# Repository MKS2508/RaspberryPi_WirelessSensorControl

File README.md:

# RaspberryPi_WirelessSensorControl

**Apache server running on a _raspberry pi_ displaying data received by sensors(arduino) over zigbee protocol**

*Sensor 1: Battery powered wireless temperature & humidity sensor board: DHT11 + Arduino pro mini + Xbee*

          Front side:

          Back side:

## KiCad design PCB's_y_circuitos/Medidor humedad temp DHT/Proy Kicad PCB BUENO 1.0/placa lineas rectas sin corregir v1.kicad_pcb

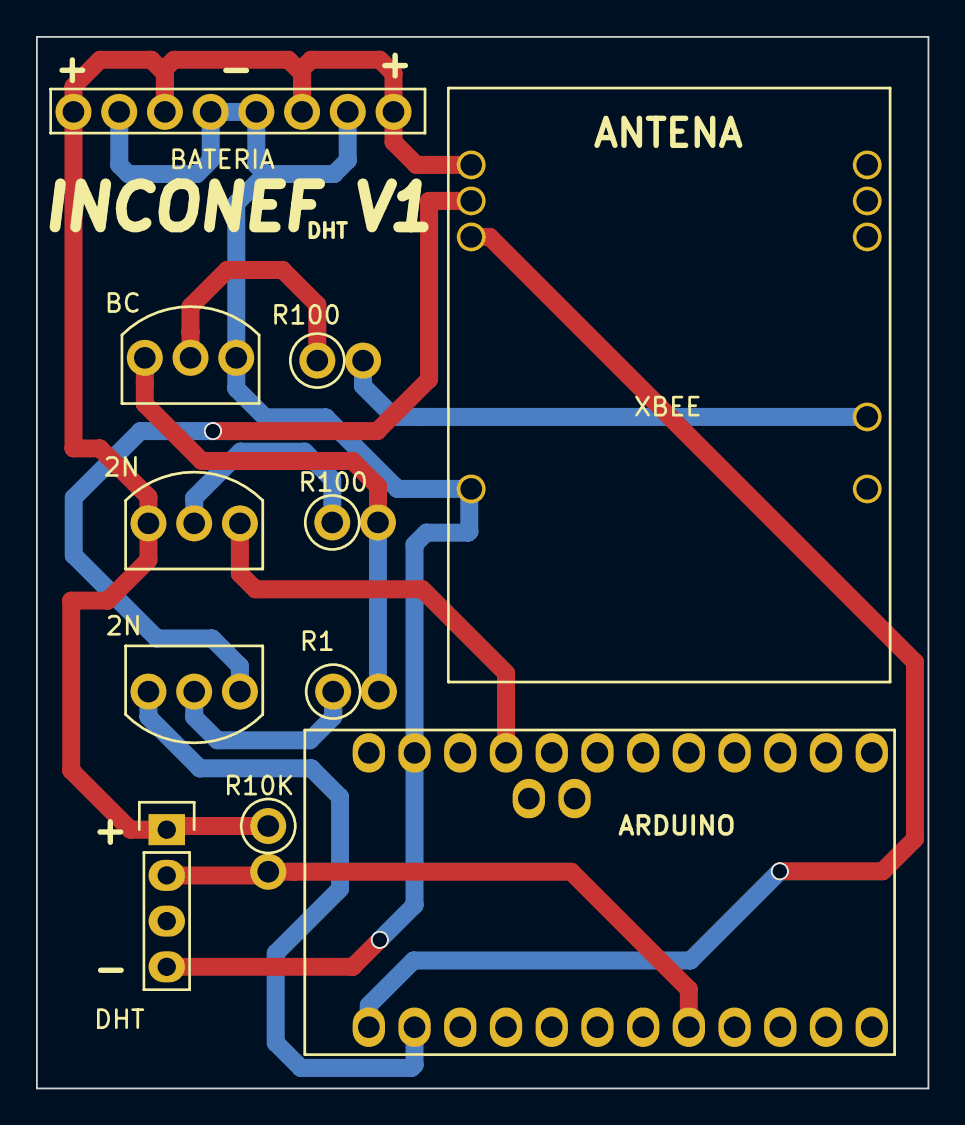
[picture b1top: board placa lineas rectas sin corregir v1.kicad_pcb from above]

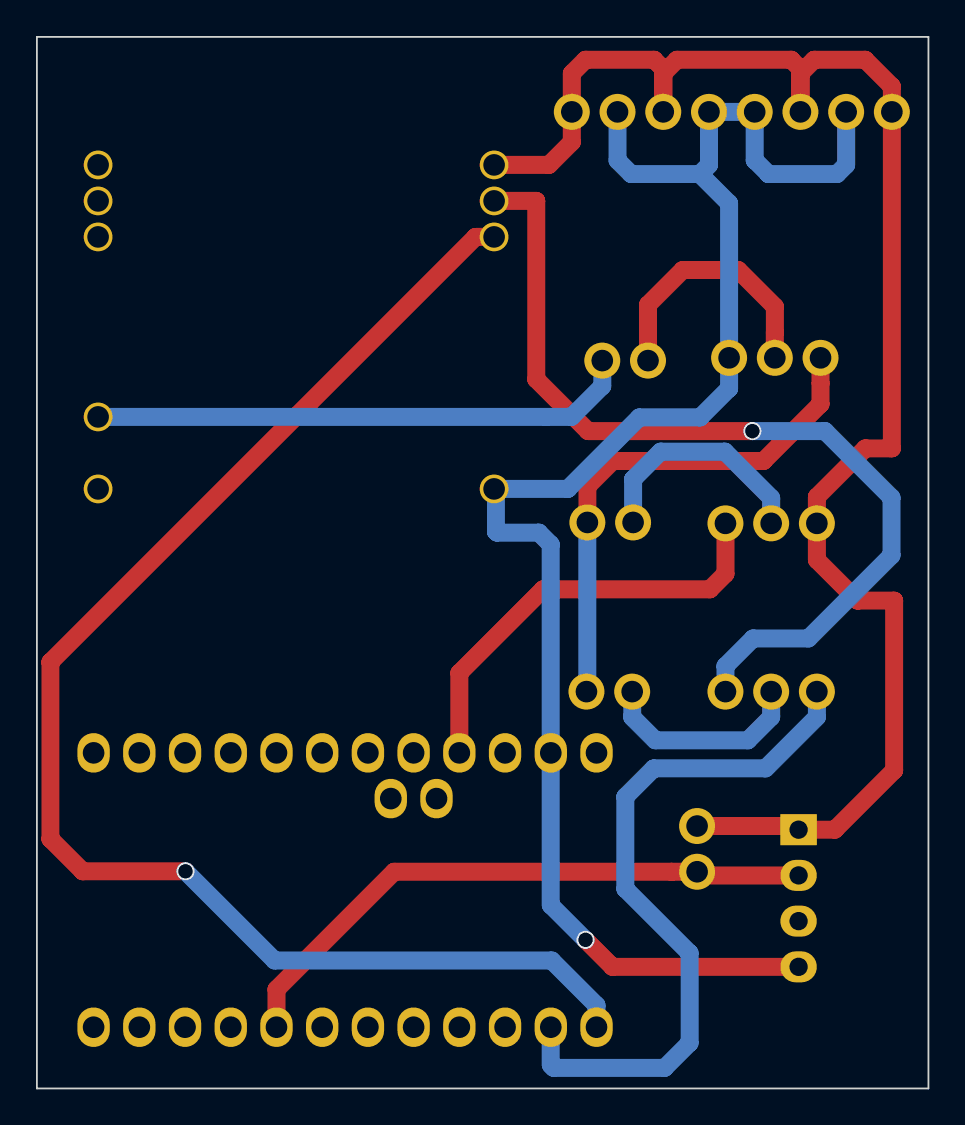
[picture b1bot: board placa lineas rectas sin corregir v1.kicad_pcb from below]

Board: 2 copper layers, 49.5 x 58.4 mm, 11 parts (2 on the bottom side), 12 nets.

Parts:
2N, 2N#2: Transistor1
 R10K: ResitenciaVertical
ARDUINO: ArduinoProMini
BATERIA: PinesBateria
BC: Transistor
DHT: DHT22_Temperature_Humidity
R1, R100, R100#2: ResitenciaVertical
XBEE: XBEE

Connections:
3.7V: 2N.1, R10K.1, BATERIA.1, BATERIA.3, BATERIA.6, BATERIA.8, DHT.1, XBEE.1
3.7V_OUT-T: 2N.3, ARDUINO.16
GND: ARDUINO.14, BATERIA.2, BATERIA.4, BATERIA.5, BATERIA.7, BC.3, DHT.4, XBEE.4
unnamed: BC.2, R100#2.1
unnamed: 2N#2.2, R1.1
unnamed: 2N.2, R100.1
PINOUT_TRANSISTOR: R100#2.2, XBEE.8
RX_ARDUINO: 2N#2.3, ARDUINO.11
RX_XBEE: ARDUINO.12, XBEE.3
SENS_DATA: R10K.2, ARDUINO.5, DHT.2
Salida_2T: BC.1, R1.2, R100.2
TX_XBEE: 2N#2.1, XBEE.2

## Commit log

2020-11-10 primer commit
2026-04-27 chore: tell Linguist these .nc files are FlatCAM G-code, not nesC
2026-04-27 chore: also mark .ino + KiCad files as vendored/generated
